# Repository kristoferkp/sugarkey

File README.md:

# sugarkey

A FIDO2 compliant security key powered by my sugar addiction (and RP2354).
Firmware is [Pico Keys](https://github.com/polhenarejos/pico-fido) by Pol Henarejos.

Done in collaboration with [Blueprint by Hack Club](https://blueprint.hackclub.com/r/1569?ref=r).

## Features
* Powered by RP2354 with 2 MB of on-chip flash and built in security features.
* Open Source
* Compact (around 3cm x 2cm)
* Protective case

## Getting started
* Have your sugarkey with you (JLCPCB fabrication files are in the production folder)
* Plug in your sugarkey while holding down BOOTSEL button.
* Download the latest [Pico Keys](https://www.picokeys.com/getting-started/) firmware for the Raspberry Pi Pico 2.
* Copy the downloaded .uf2 file to the Picoboot storage mount.
* Commisson your sugarkey [here](https://www.picokeys.com/pico-commissioner/).
* The LED is a WS2812 on GPIO 16.
* Plug the key into your device, it will show up as a passkey.

## Hardware
* MCU: RP2354A
* LED: WS2812 or similar
* Raspberry Pi recommended LDO, inductor, crystal oscillator.

## **Disclaimer!**
This isn't a finished product and shouldn't be trusted with super important stuff.
I am in no way responsible for lost data.

## Schematic

## PCB

## Picture of the JLCPCB cart

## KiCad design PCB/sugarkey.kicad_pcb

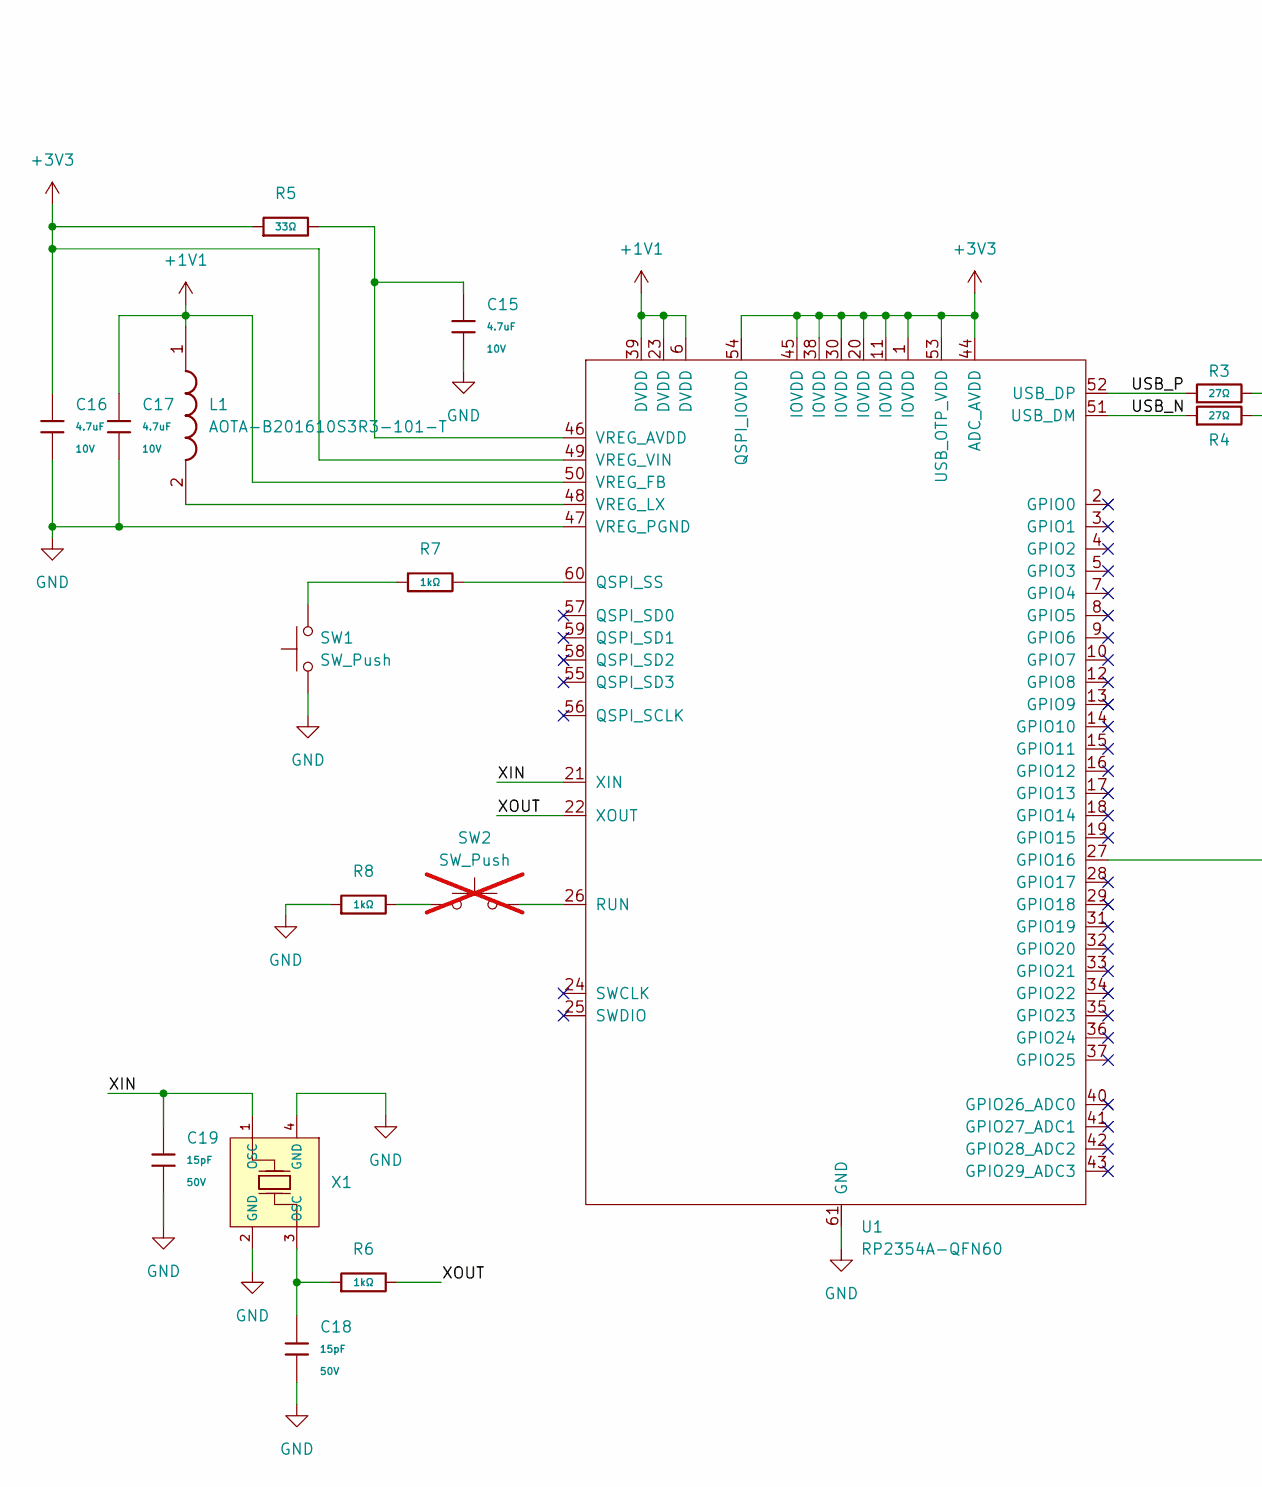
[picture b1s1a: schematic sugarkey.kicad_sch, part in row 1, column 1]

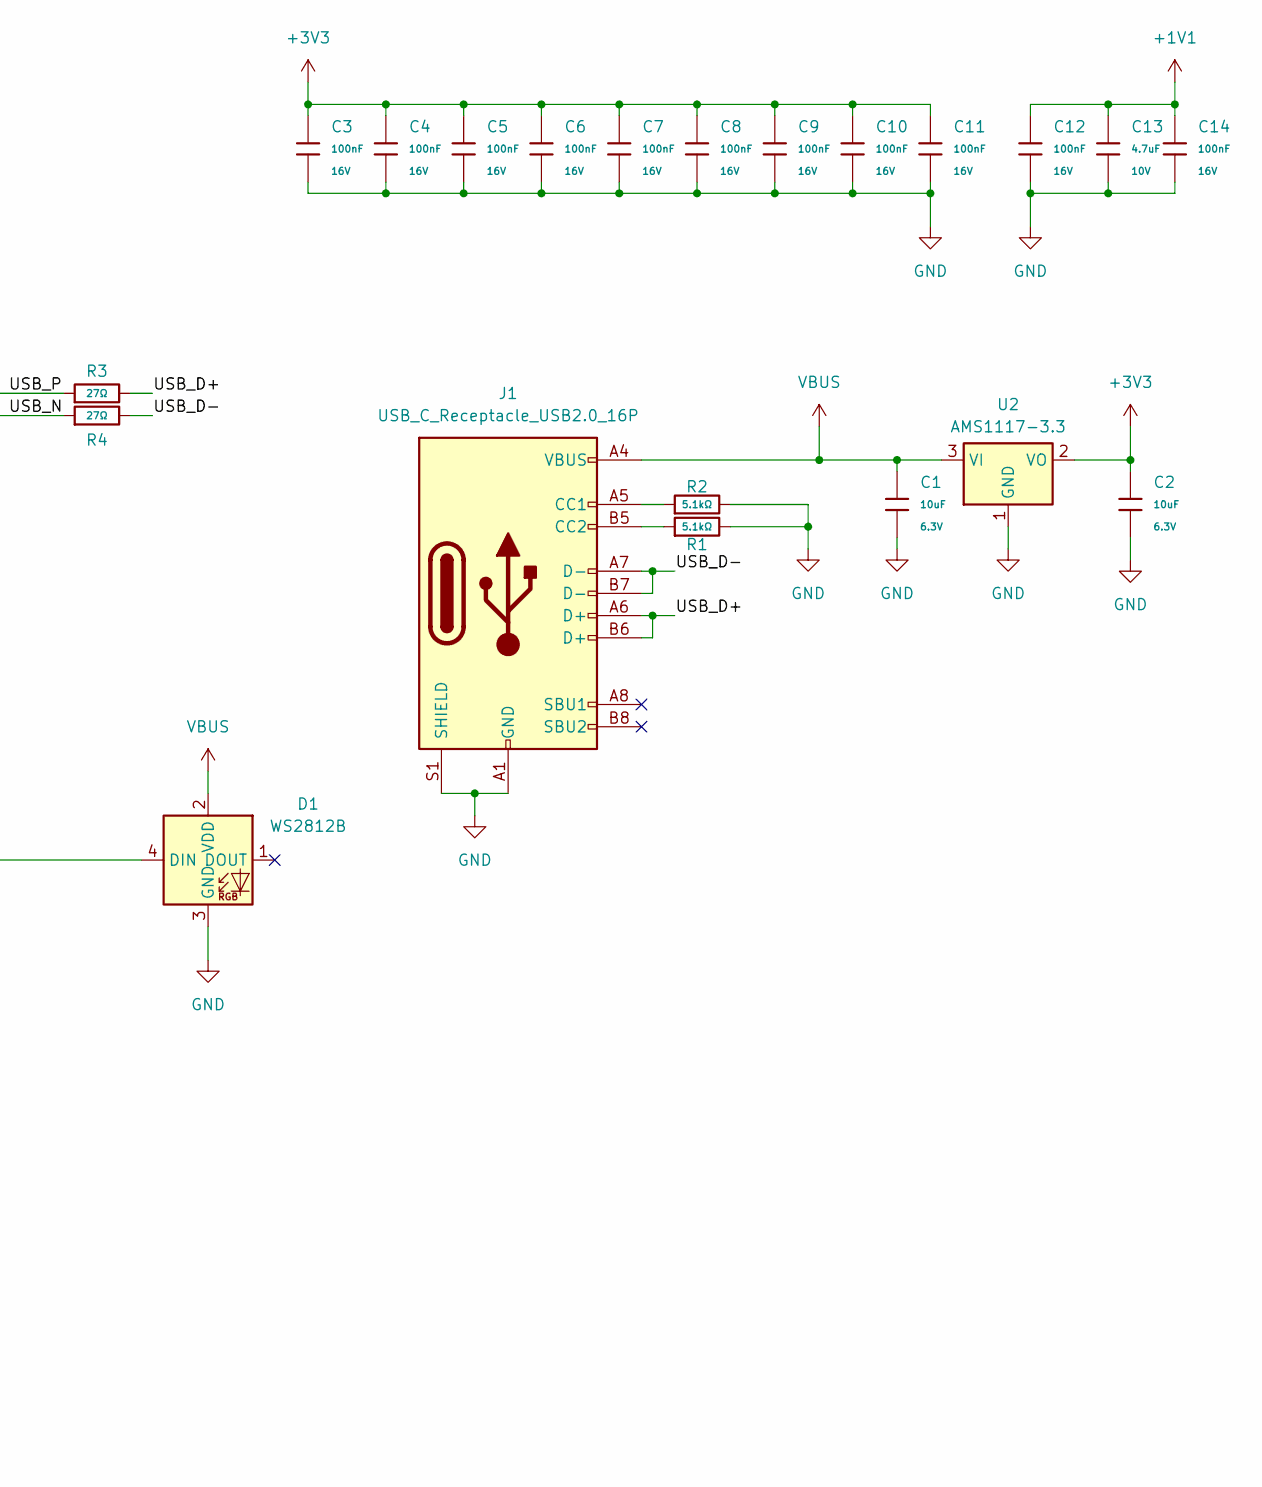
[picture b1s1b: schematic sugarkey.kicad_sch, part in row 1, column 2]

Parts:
C1, C2: 10uF; C_0402; Voltage Rated 6.3V; Tolerance ±20%; Part CL05A106MQ5NUNC; LCSC C15525
C3, C4, C5, C6, C7, C8, C9, C10, C11, C12, C14: 100nF; C_0402; Voltage Rated 16V; Tolerance ±10%; Part CL05B104KO5NNNC; LCSC C1525
C13, C15, C16, C17: 4.7uF; C_0402; Voltage Rated 10V; Tolerance ±20%; Part CL05A475MP5NRNC; LCSC C23733
C18, C19: 15pF; C_0402; Voltage Rated 50V; Tolerance ±5%; Part 0402CG150J500NT; LCSC C1548
D1: WS2812B; LED-SMD_4P-L1.6-W1.5_XL-1615RGBC-WS2812B; LCSC C5349954
J1: USB_C_Receptacle_USB2.0_16P; USB_C_Receptacle_HRO_TYPE-C-31-M-12
L1: AOTA-B201610S3R3-101-T; AOTAB201610S3R3101T; Manufacturer_Part_Number AOTA-B201610S3R3-101-T; Mouser Part Number 815-AB201610S3R3101T
R1, R2: 5.1kΩ; R_0402; Overload Voltage (Max) 50V; Tolerance ±1%; Part 0402WGF5101TCE; LCSC C25905
R3, R4: 27Ω; R_0402; Overload Voltage (Max) 50V; Tolerance ±1%; Part 0402WGF2702TCE; LCSC C25771
R5: 33Ω; R_0402; Overload Voltage (Max) 50V; Tolerance ±1%; Part 0402WGF330JTCE; LCSC C25105
R6, R7, R8: 1kΩ; R_0402; Overload Voltage (Max) 50V; Tolerance ±1%; Part 0402WGF1001TCE; LCSC C11702
SW1: SW_Push; SW_TS-1088-AR02016
SW2: SW_Push; SW_TS-1088-AR02016; not fitted
U1: RP2354A-QFN60; RP2350A_QFN-60_EP_7.75x7.75_Pitch0.4mm
U2: AMS1117-3.3; SOT-223-3_TabPin2
X1: X322512MSB4SI; CRYSTAL-SMD_4P-L3.2-W2.5-BL; Frequency Tolerance ±10ppm; Part X322512MSB4SI; LCSC C9002

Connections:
+1V1: C12.1, C13.1, C14.1, C17.1, L1.1, U1.6 (DVDD), U1.23 (DVDD), U1.39 (DVDD), U1.50 (VREG_FB)
+3V3: C2.1, C3.1, C4.1, C5.1, C6.1, C7.1, C8.1, C9.1, C10.1, C11.1, C16.2, R5.1, U1.1 (IOVDD), U1.11 (IOVDD), U1.20 (IOVDD), U1.30 (IOVDD), U1.38 (IOVDD), U1.44 (ADC_AVDD), U1.45 (IOVDD), U1.49 (VREG_VIN), U1.53 (USB_OTP_VDD), U1.54 (QSPI_IOVDD), U2.2 (VO)
/USB_D+: J1.A6 (D+), J1.B6 (D+), R3.2
/USB_D-: J1.A7 (D-), J1.B7 (D-), R4.2
/USB_N: R4.1, U1.51 (USB_DM)
/USB_P: R3.1, U1.52 (USB_DP)
/XIN: C19.1, U1.21 (XIN), X1.1 (OSC)
/XOUT: R6.2, U1.22 (XOUT)
GND: C1.2, C2.2, C3.2, C4.2, C5.2, C6.2, C7.2, C8.2, C9.2, C10.2, C11.2, C12.2, C13.2, C14.2, C15.2, C16.1, C17.2, C18.2, C19.2, D1.3 (GND), J1.A1 (GND), J1.A12 (GND), J1.B1 (GND), J1.B12 (GND), J1.S1 (SHIELD), R1.2, R2.2, R8.1, SW1.1, U1.47 (VREG_PGND), U1.61 (GND), U2.1 (GND), X1.2 (GND), X1.4 (GND)
unnamed: C18.1, R6.1, X1.3 (OSC)
unnamed: D1.4 (DIN), U1.27 (GPIO16)
unnamed: J1.A5 (CC1), R2.1
unnamed: J1.B5 (CC2), R1.1
unnamed: R7.1, SW1.2
unnamed: R8.2, SW2.1
unnamed: R7.2, U1.60 (QSPI_SS)
unnamed: SW2.2, U1.26 (RUN)
unnamed: C15.1, R5.2, U1.46 (VREG_AVDD)
unnamed: L1.2, U1.48 (VREG_LX)
VBUS: C1.1, D1.2 (VDD), J1.A4 (VBUS), J1.A9 (VBUS), J1.B4 (VBUS), J1.B9 (VBUS), U2.3 (VI)

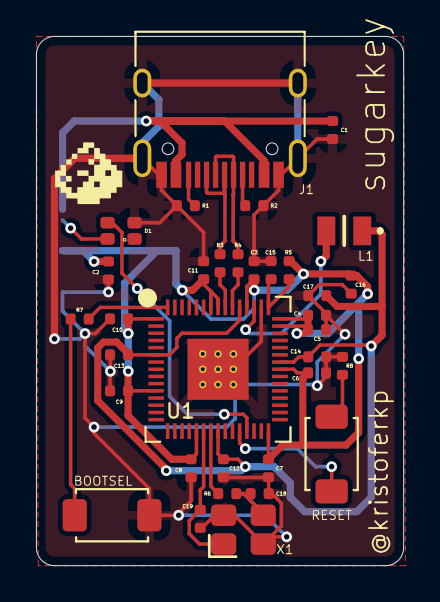
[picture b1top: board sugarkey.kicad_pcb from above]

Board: 2 copper layers, 20.4 x 29.4 mm, 35 parts (1 on the bottom side), 20 nets.

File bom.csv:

Designator,Footprint,Quantity,Value,LCSC Part #
"C1, C2",C_0402,2,10uF,C15525
"C10, C11, C12, C14, C3, C4, C5, C6, C7, C8, C9",C_0402,11,100nF,C1525
"C13, C15, C16, C17",C_0402,4,4.7uF,C23733
"C18, C19",C_0402,2,15pF,C1548
D1,LED-SMD_4P-L1.6-W1.5_XL-1615RGBC-WS2812B,1,WS2812B,C5349954
J1,USB_C_Receptacle_HRO_TYPE-C-31-M-12,1,USB_C_Receptacle_USB2.0_16P,
L1,AOTAB201610S3R3101T,1,AOTA-B201610S3R3-101-T,
"R1, R2",R_0402,2,5.1kΩ,C25905
"R3, R4",R_0402,2,27Ω,C25771
R5,R_0402,1,33Ω,C25105
"R6, R7, R8",R_0402,3,1kΩ,C11702
"SW1, SW2",SW_TS-1088-AR02016,2,SW_Push,
U1,RP2350A_QFN-60_EP_7.75x7.75_Pitch0.4mm,1,RP2354A-QFN60,
U2,SOT-223-3_TabPin2,1,AMS1117-3.3,
X1,CRYSTAL-SMD_4P-L3.2-W2.5-BL,1,ABM8-272-T3,C20625731

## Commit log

2025-10-25 added needed files
2025-10-25 updated bom, readme
